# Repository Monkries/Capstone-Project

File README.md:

# Capstone-Project
The lathe is arguably the most important machine tool in engineering history, and one of its defining features is the ability to cut threads. For hundreds of years, this has been accomplished by using gears to link the movement of the cutting tool to the movement of the spinning workpiece. To cut finer or coarser threads, the machinist must vary this gear ratio.This system works, but it has limitations. It is poorly suited for small benchtop machines, because the gearbox parts end up extremely small and expensive to manufacture. It is also inconvenient to adjust; the machinist must read a chart and physically add and remove gears from the geartrain. On larger lathes, this inconvenience is reduced using a simple transmission, allowing the machinist to shift several levers according to a chart, but this is more expensive, and more difficult to scale down to smaller machines.This project aims to replace this gearbox with electronics. This will eliminate the need to physically move gears around to adjust the system; instead, machinists will simply type in the desiredthread pitch into the control panel. Additionally, this system will be much more cost-effective and accessible on small benchtop lathes, where the traditional gearbox approach is impractical.

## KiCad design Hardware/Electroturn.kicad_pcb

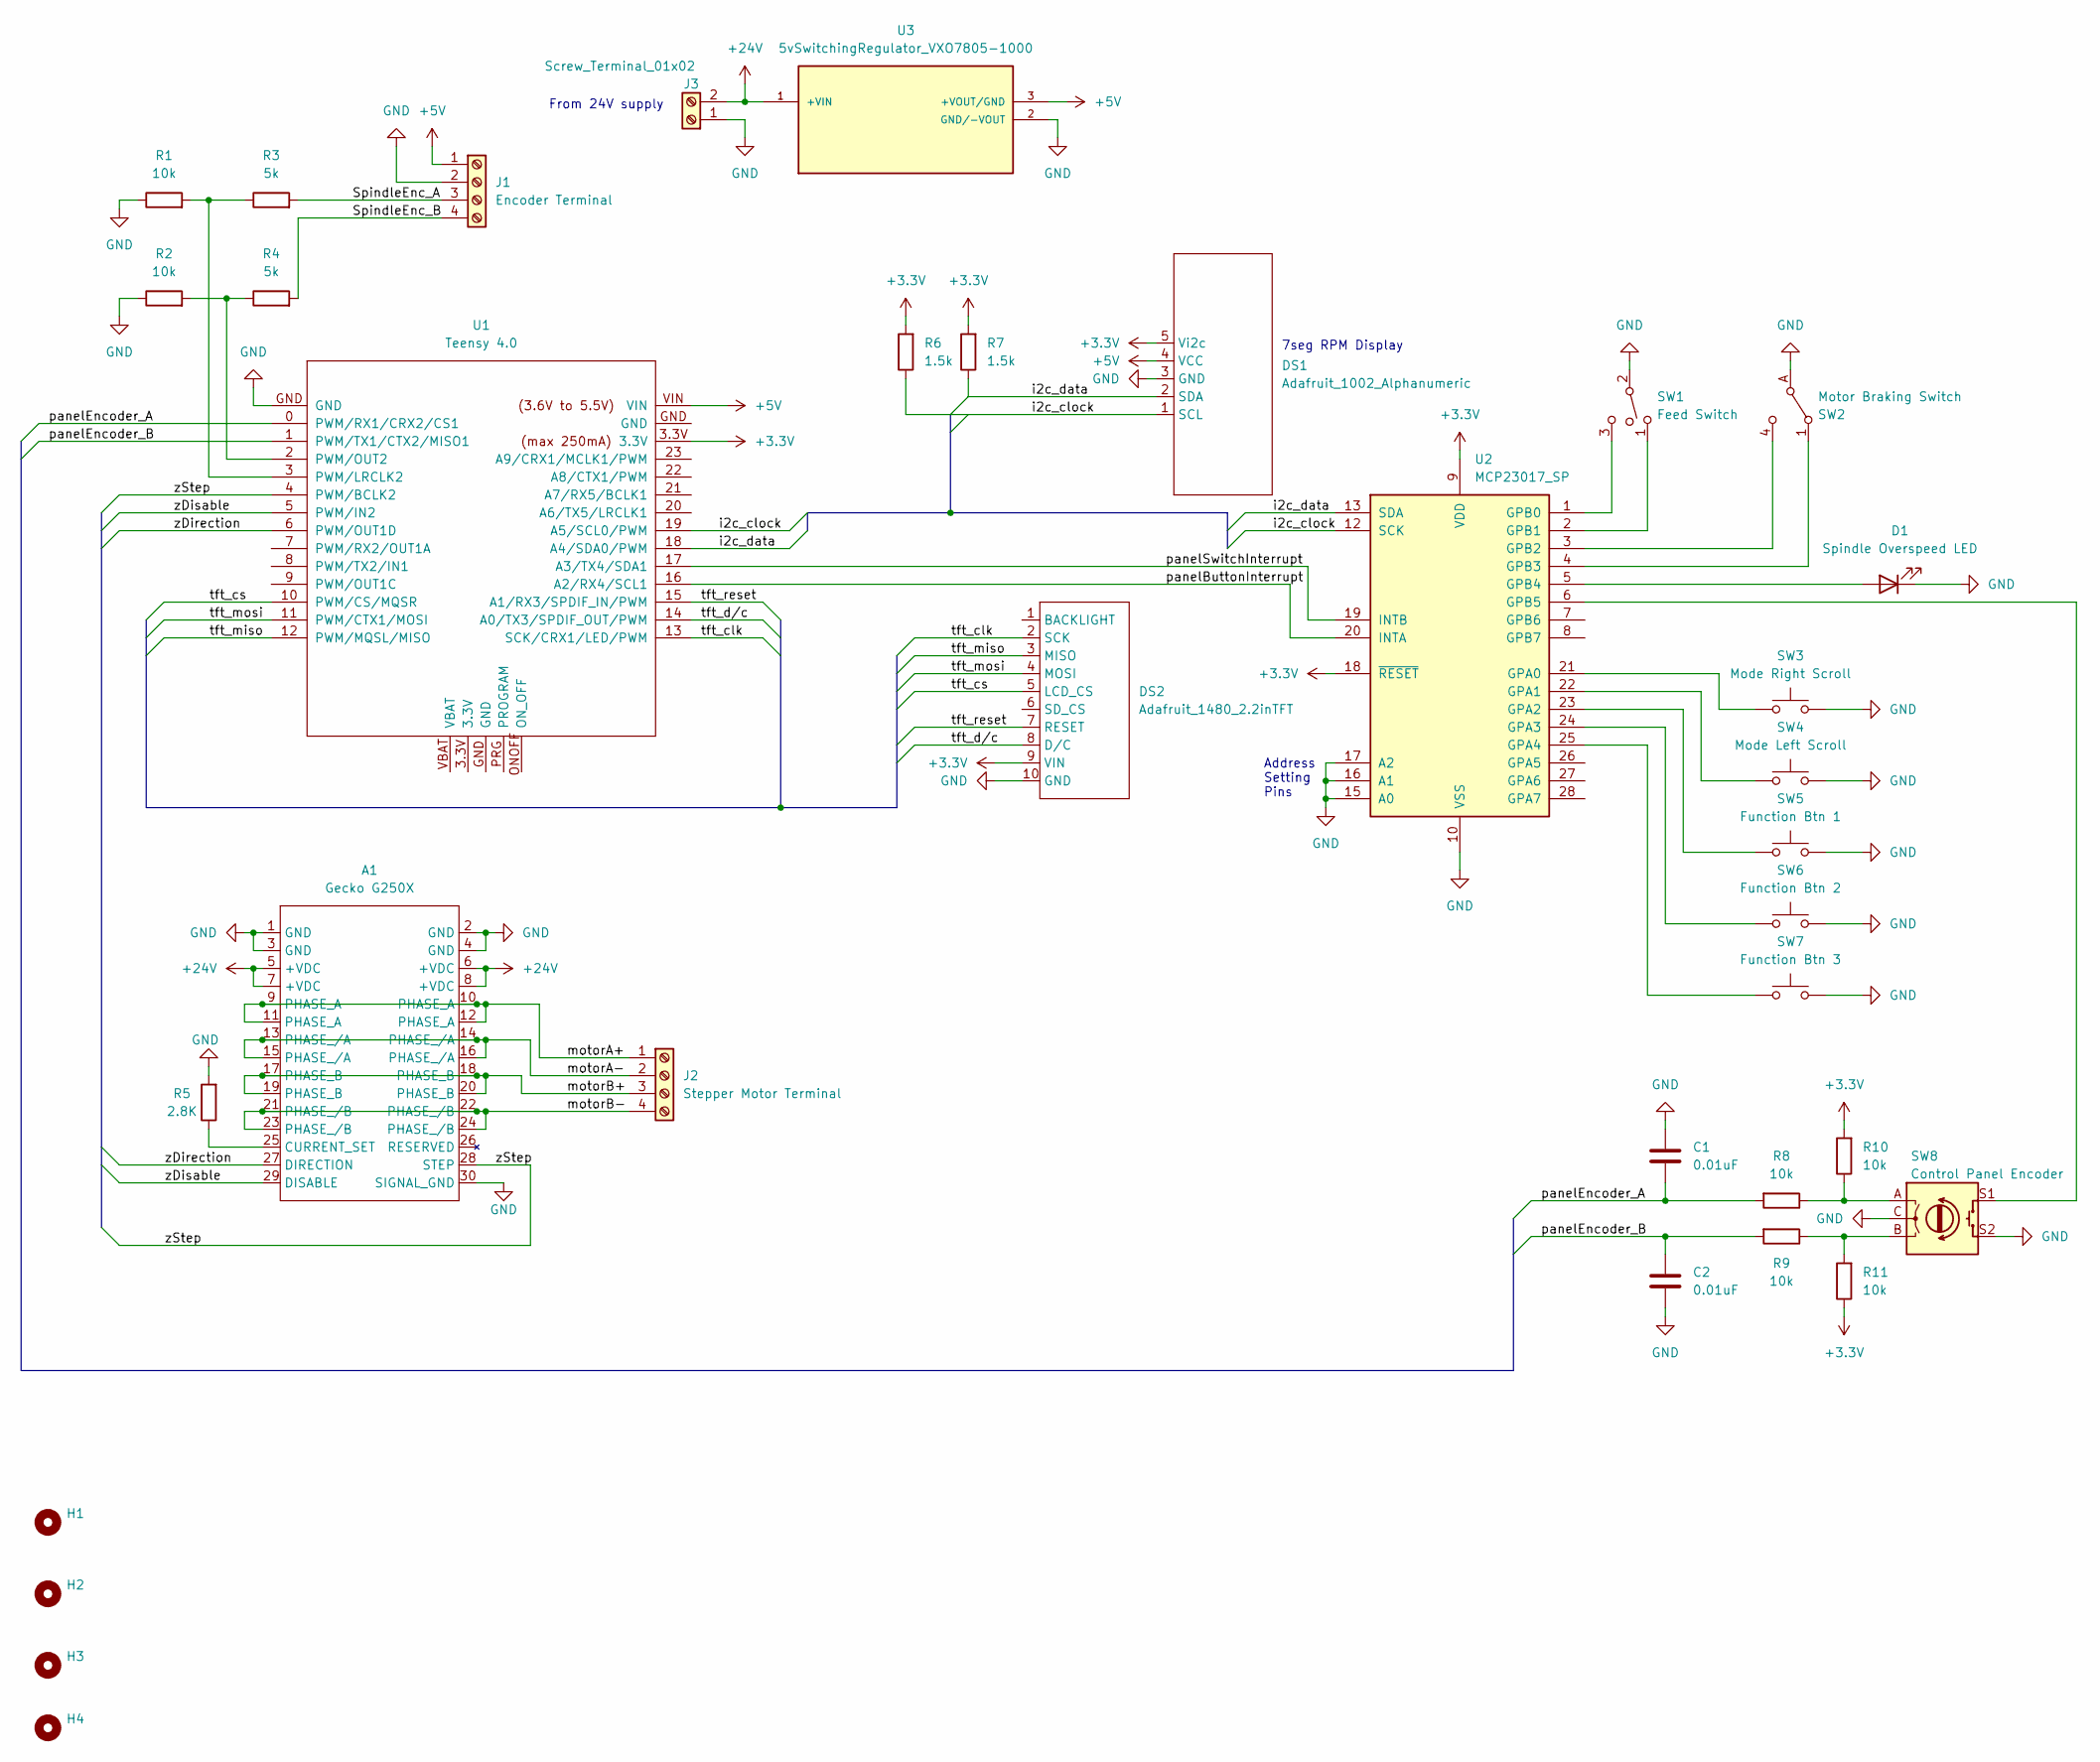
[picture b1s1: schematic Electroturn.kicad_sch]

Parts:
A1: Gecko G250X; GeckoG250XR2_WithHeatsink
C1, C2: 0.01uF; C_Disc_D6.0mm_W2.5mm_P5.00mm
D1: Spindle Overspeed LED; LED_D5.0mm
DS1: Adafruit_1002_Alphanumeric; Adafruit1002_0.54inAlphanumericBackpack
DS2: Adafruit_1480_2.2inTFT; Adafruit1480_TFTwithHeaders
H1, H2, H3, H4: (no value)
J1: Encoder Terminal; ScrewTerminal4_OSTVN04A150
J2: Stepper Motor Terminal; ScrewTerminal4_OSTVN04A150
J3: Screw_Terminal_01x02; 01x02ScrewTerm_OSTVN02A150
R1, R2, R8, R9, R10, R11: 10k; R_Axial_DIN0411_L9.9mm_D3.6mm_P12.70mm_Horizontal
R3, R4: 5k; R_Axial_DIN0411_L9.9mm_D3.6mm_P12.70mm_Horizontal
R5: 2.8K; R_Axial_DIN0411_L9.9mm_D3.6mm_P12.70mm_Horizontal
R6, R7: 1.5k; R_Axial_DIN0411_L9.9mm_D3.6mm_P12.70mm_Horizontal
SW1: Feed Switch; SPDT_OnOffOn_ToggleSwitch_fromECEdepartment_CircularPads
SW2: Motor Braking Switch; SW_SPDT_CK_ A11405RNZQ
SW3: Mode Right Scroll; SW_PUSH_6mm_H9.5mm
SW4: Mode Left Scroll; SW_PUSH_6mm_H9.5mm
SW5: Function Btn 1; SW_PUSH_6mm_H9.5mm
SW6: Function Btn 2; SW_PUSH_6mm_H9.5mm
SW7: Function Btn 3; SW_PUSH_6mm_H9.5mm
SW8: Control Panel Encoder; CUIDevices_ACZ11BR1E20FD112C
U1: Teensy 4.0; Teensy40_OnFemaleHeaders
U2: MCP23017_SP; DIP-28_W7.62mm
U3: 5vSwitchingRegulator_VXO7805-1000; 5vSwitchingRegulator_CONV_VXO7805-1000; PARTREV 1.0

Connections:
+3V3: DS1.5 (Vi2c), DS2.9 (VIN), R6.2, R7.2, R10.2, R11.1, U1.3.3V, U2.9 (VDD), U2.18 (~RESET)
+5V: DS1.4 (VCC), J1.1, U1.VIN, U3.3 (+VOUT/GND)
+24V: A1.5 (+VDC), A1.6 (+VDC), A1.7 (+VDC), A1.8 (+VDC), J3.2, U3.1 (+VIN)
/SpindleEnc_A: J1.3, R3.2
/SpindleEnc_B: J1.4, R4.2
/i2c_clock: DS1.1 (SCL), R6.1, U1.19 (A5/SCL0/PWM), U2.12 (SCK)
/i2c_data: DS1.2 (SDA), R7.1, U1.18 (A4/SDA0/PWM), U2.13 (SDA)
/motorA+: A1.9 (PHASE_A), A1.10 (PHASE_A), A1.11 (PHASE_A), A1.12 (PHASE_A), J2.1
/motorA-: A1.13 (PHASE_/A), A1.14 (PHASE_/A), A1.15 (PHASE_/A), A1.16 (PHASE_/A), J2.2
/motorB+: A1.17 (PHASE_B), A1.18 (PHASE_B), A1.19 (PHASE_B), A1.20 (PHASE_B), J2.3
/motorB-: A1.21 (PHASE_/B), A1.22 (PHASE_/B), A1.23 (PHASE_/B), A1.24 (PHASE_/B), J2.4
/panelButtonInterrupt: U1.16 (A2/RX4/SCL1), U2.20 (INTA)
/panelEncoder_A: C1.2, R8.2, U1.0 (PWM/RX1/CRX2/CS1)
/panelEncoder_B: C2.1, R9.2, U1.1 (PWM/TX1/CTX2/MISO1)
/panelSwitchInterrupt: U1.17 (A3/TX4/SDA1), U2.19 (INTB)
/tft_clk: DS2.2 (SCK), U1.13 (SCK/CRX1/LED/PWM)
/tft_cs: DS2.5 (LCD_CS), U1.10 (PWM/CS/MQSR)
/tft_d/c: DS2.8 (D/C), U1.14 (A0/TX3/SPDIF_OUT/PWM)
/tft_miso: DS2.3 (MISO), U1.12 (PWM/MQSL/MISO)
/tft_mosi: DS2.4 (MOSI), U1.11 (PWM/CTX1/MOSI)
/tft_reset: DS2.7 (RESET), U1.15 (A1/RX3/SPDIF_IN/PWM)
/zDirection: A1.27 (DIRECTION), U1.6 (PWM/OUT1D)
/zDisable: A1.29 (DISABLE), U1.5 (PWM/IN2)
/zStep: A1.28 (STEP), U1.4 (PWM/BCLK2)
GND: A1.1 (GND), A1.2 (GND), A1.3 (GND), A1.4 (GND), A1.30 (SIGNAL_GND), C1.1, C2.2, D1.1 (K), DS1.3 (GND), DS2.10 (GND), J1.2, J3.1, R1.1, R2.1, R5.2, SW1.2, SW2.A, SW3.2, SW4.2, SW5.2, SW6.2, SW7.2, SW8.C, SW8.S2, U1.GND, U2.10 (VSS), U2.15 (A0), U2.16 (A1), U2.17 (A2), U3.2 (GND/-VOUT)
unnamed: A1.25 (CURRENT_SET), R5.1
unnamed: D1.2 (A), U2.5 (GPB4)
unnamed: R1.2, R3.1, U1.3 (PWM/LRCLK2)
unnamed: R2.2, R4.1, U1.2 (PWM/OUT2)
unnamed: R8.1, R10.1, SW8.A
unnamed: R9.1, R11.2, SW8.B
unnamed: SW1.1, U2.2 (GPB1)
unnamed: SW1.3, U2.1 (GPB0)
unnamed: SW2.1, U2.4 (GPB3)
unnamed: SW2.4, U2.3 (GPB2)
unnamed: SW3.1, U2.21 (GPA0)
unnamed: SW4.1, U2.22 (GPA1)
unnamed: SW5.1, U2.23 (GPA2)
unnamed: SW6.1, U2.24 (GPA3)
unnamed: SW7.1, U2.25 (GPA4)
unnamed: SW8.S1, U2.6 (GPB5)

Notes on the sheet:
7seg RPM Display
From 24V supply
Address Setting Pins

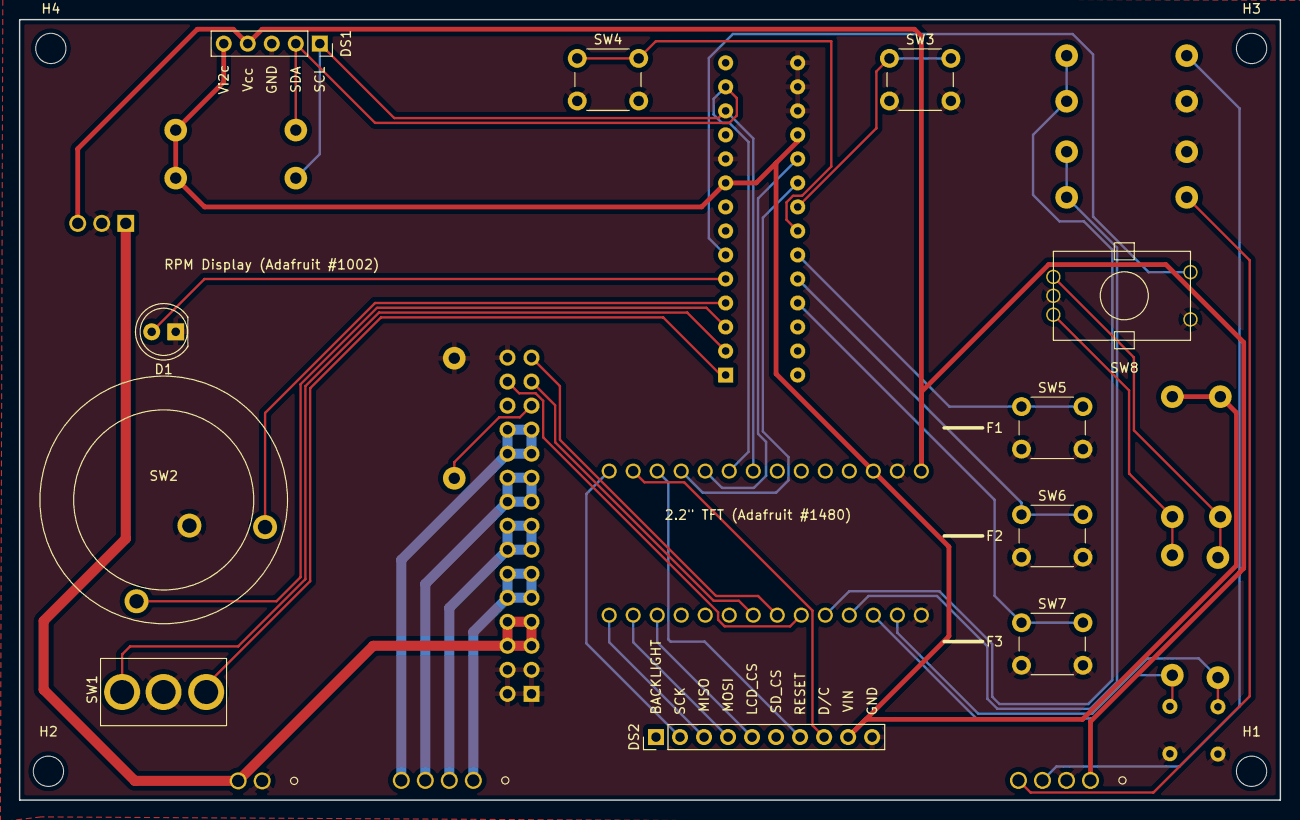
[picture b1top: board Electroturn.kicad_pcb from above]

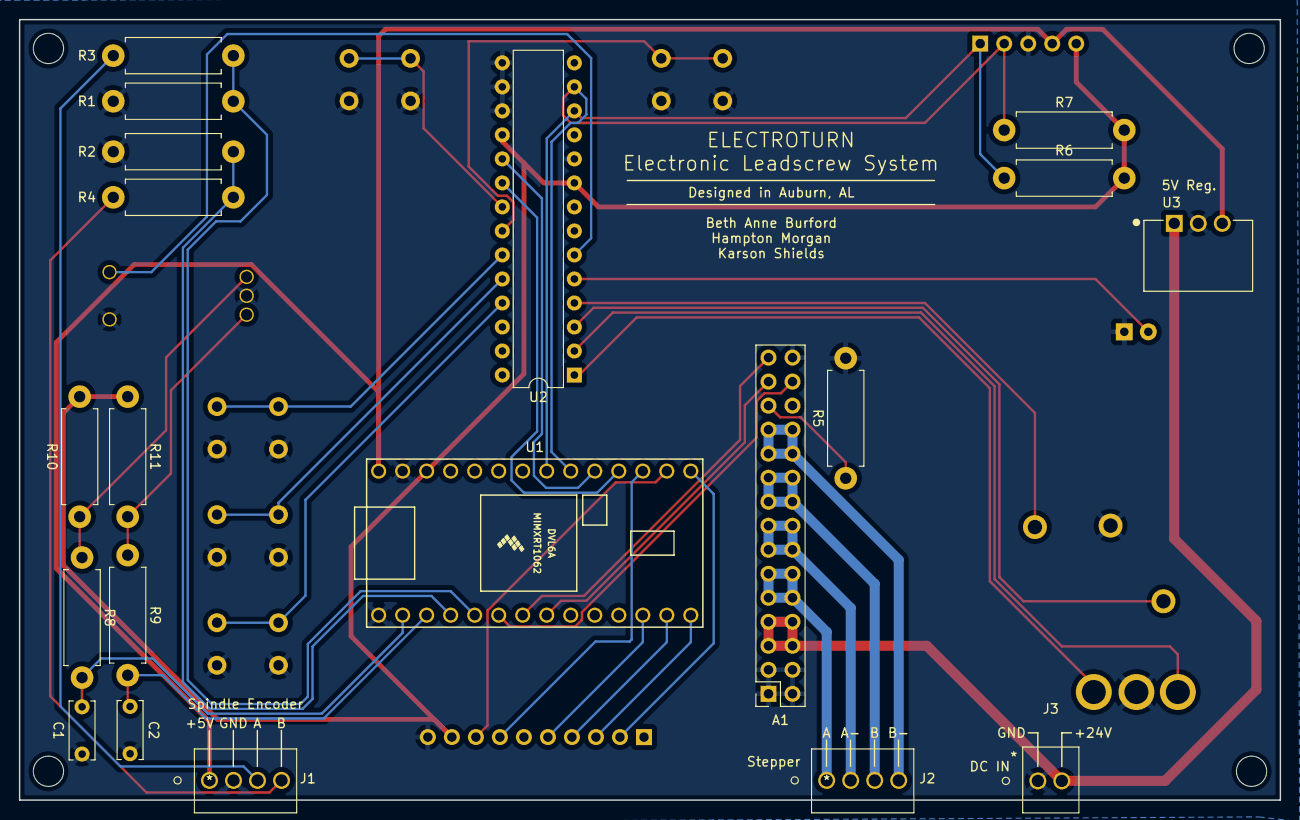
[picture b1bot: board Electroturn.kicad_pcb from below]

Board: 2 copper layers, 133.4 x 82.5 mm, 35 parts (20 on the bottom side), 41 nets.

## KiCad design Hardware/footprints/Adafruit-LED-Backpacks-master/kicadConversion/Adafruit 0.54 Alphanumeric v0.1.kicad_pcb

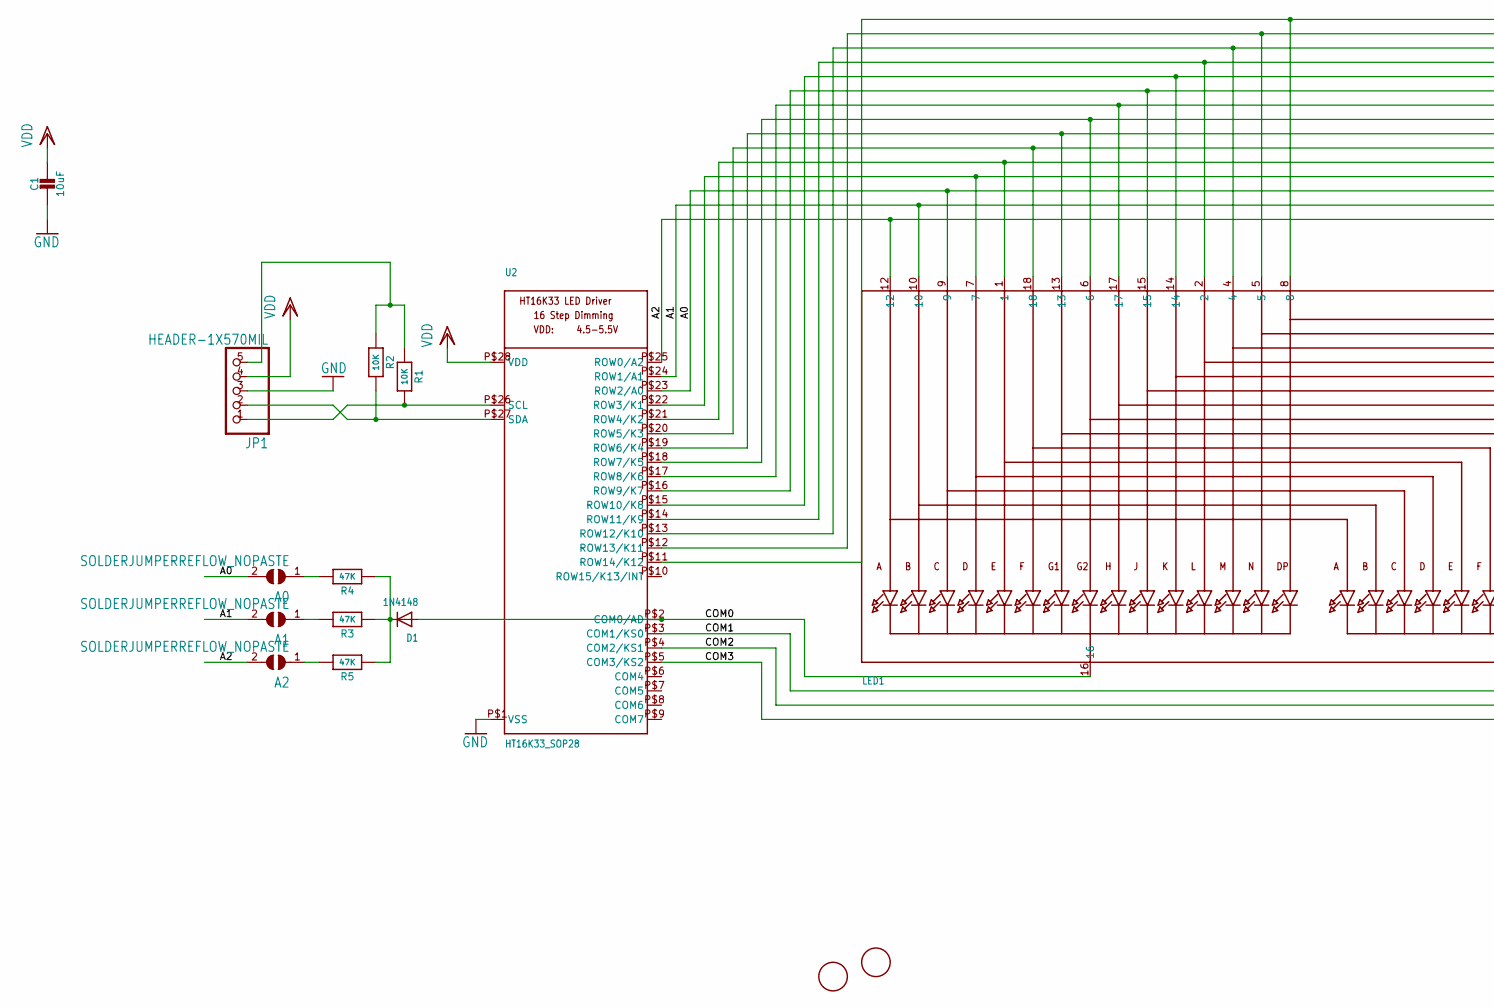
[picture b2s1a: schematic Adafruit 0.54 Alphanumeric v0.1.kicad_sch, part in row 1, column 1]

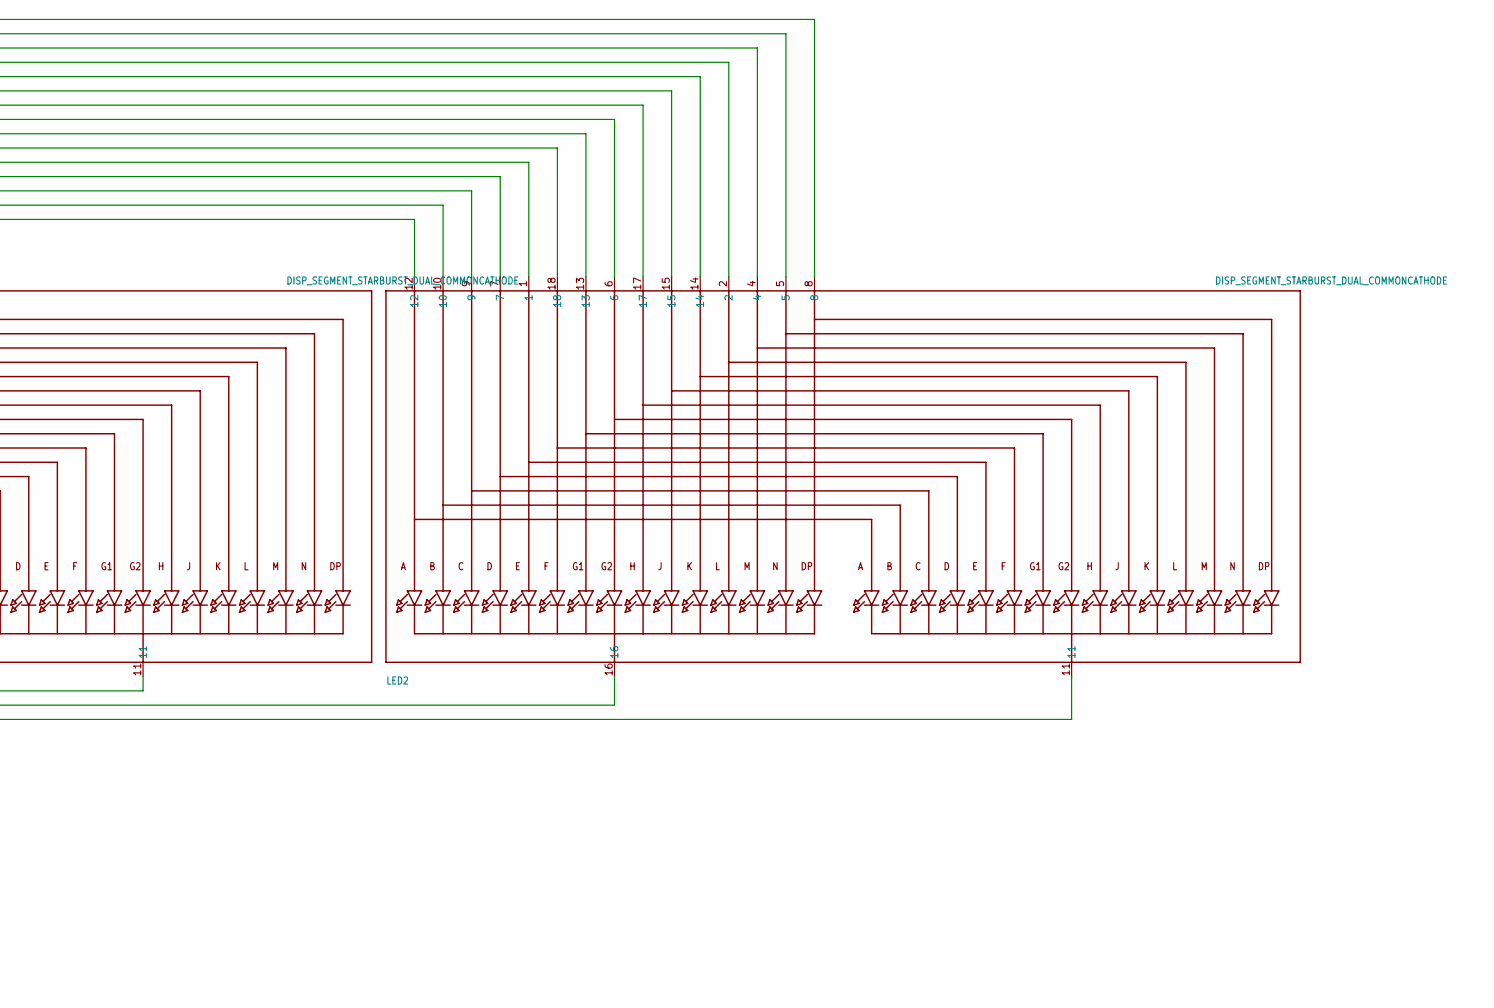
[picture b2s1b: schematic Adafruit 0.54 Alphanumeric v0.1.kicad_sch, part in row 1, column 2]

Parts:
A0, A1, A2: SOLDERJUMPERREFLOW_NOPASTE; SOLDERJUMPER_REFLOW_NOPASTE
C1: 10uF; 0805-NO
D1: 1N4148; SOD-323F
JP1: HEADER-1X570MIL; 1X05_ROUND_70
LED1, LED2: DISP_SEGMENT_STARBURST_DUAL_COMMONCATHODE; SEGMENT_STARTBUST_DUAL_KWA-541CBB
R1, R2: 10K; 0805-NO
R3, R4, R5: 47K; 0805-NO
U2: HT16K33_SOP28; SOP28_300MIL
U$1, U$2: FIDUCIAL; FIDUCIAL_1MM

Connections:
A0: A0.2, LED1.9, LED2.9, U2.P$23 (ROW2/A0)
A1: A1.2, LED1.10, LED2.10, U2.P$24 (ROW1/A1)
A2: A2.2, LED1.12, LED2.12, U2.P$25 (ROW0/A2)
COM0: D1.A, LED1.16, U2.P$2 (COM0/AD)
COM1: LED1.11, U2.P$3 (COM1/KS0)
COM2: LED2.16, U2.P$4 (COM2/KS1)
COM3: LED2.11, U2.P$5 (COM3/KS2)
GND: C1.2, JP1.3, U2.P$1 (VSS)
unnamed: D1.C, R3.1, R4.1, R5.1
unnamed: JP1.5, R1.1, R2.1
unnamed: LED1.17, LED2.17, U2.P$17 (ROW8/K6)
unnamed: LED1.15, LED2.15, U2.P$16 (ROW9/K7)
unnamed: LED1.14, LED2.14, U2.P$15 (ROW10/K8)
unnamed: A2.1, R5.2
unnamed: LED1.2, LED2.2, U2.P$14 (ROW11/K9)
unnamed: LED1.4, LED2.4, U2.P$13 (ROW12/K10)
unnamed: LED1.7, LED2.7, U2.P$22 (ROW3/K1)
unnamed: LED1.1, LED2.1, U2.P$21 (ROW4/K2)
unnamed: LED1.18, LED2.18, U2.P$20 (ROW5/K3)
unnamed: LED1.13, LED2.13, U2.P$19 (ROW6/K4)
unnamed: LED1.5, LED2.5, U2.P$12 (ROW13/K11)
unnamed: LED1.8, LED2.8, U2.P$11 (ROW14/K12)
unnamed: LED1.6, LED2.6, U2.P$18 (ROW7/K5)
unnamed: A1.1, R3.2
unnamed: A0.1, R4.2
SCL: JP1.1, R1.2, U2.P$26 (SCL)
SDA: JP1.2, R2.2, U2.P$27 (SDA)
VDD: C1.1, JP1.4, U2.P$28 (VDD)

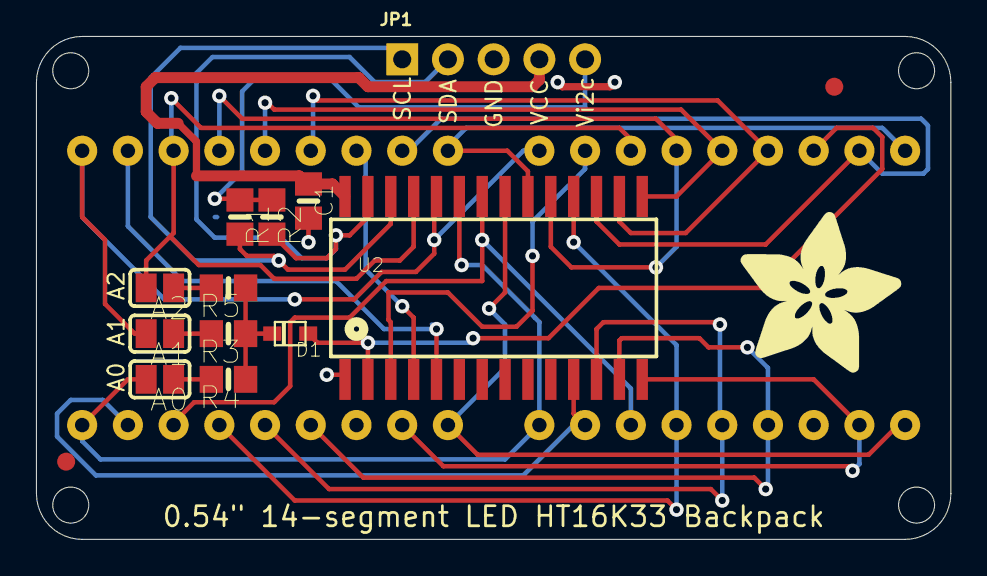
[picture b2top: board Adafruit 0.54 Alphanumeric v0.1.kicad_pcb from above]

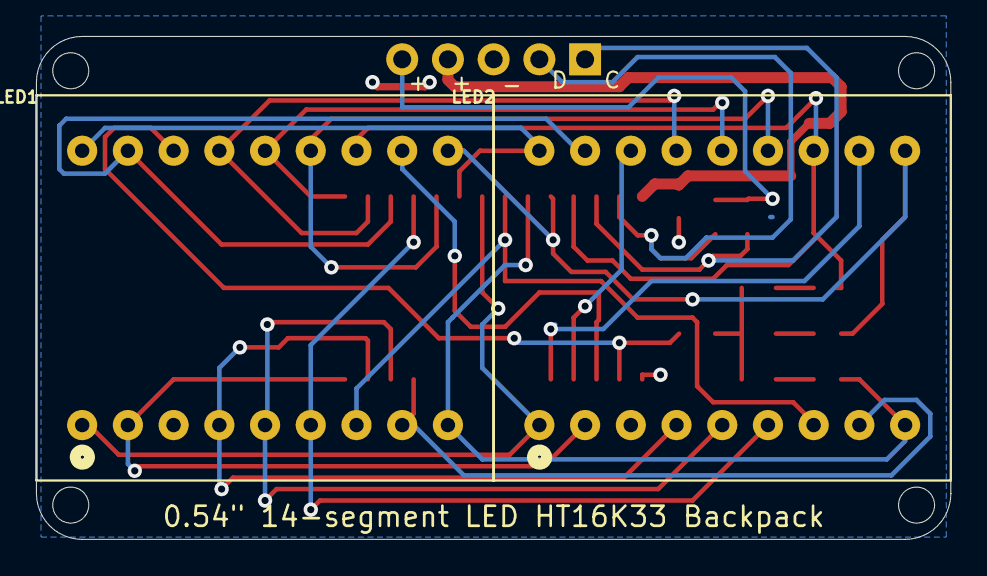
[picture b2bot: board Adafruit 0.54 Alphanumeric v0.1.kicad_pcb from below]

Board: 16 copper layers, 50.8 x 27.9 mm, 21 parts (2 on the bottom side), 28 nets.

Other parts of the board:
@HOLE0, @HOLE1, @HOLE2, @HOLE3: (no value)
U$3: ADAFRUIT_9MM

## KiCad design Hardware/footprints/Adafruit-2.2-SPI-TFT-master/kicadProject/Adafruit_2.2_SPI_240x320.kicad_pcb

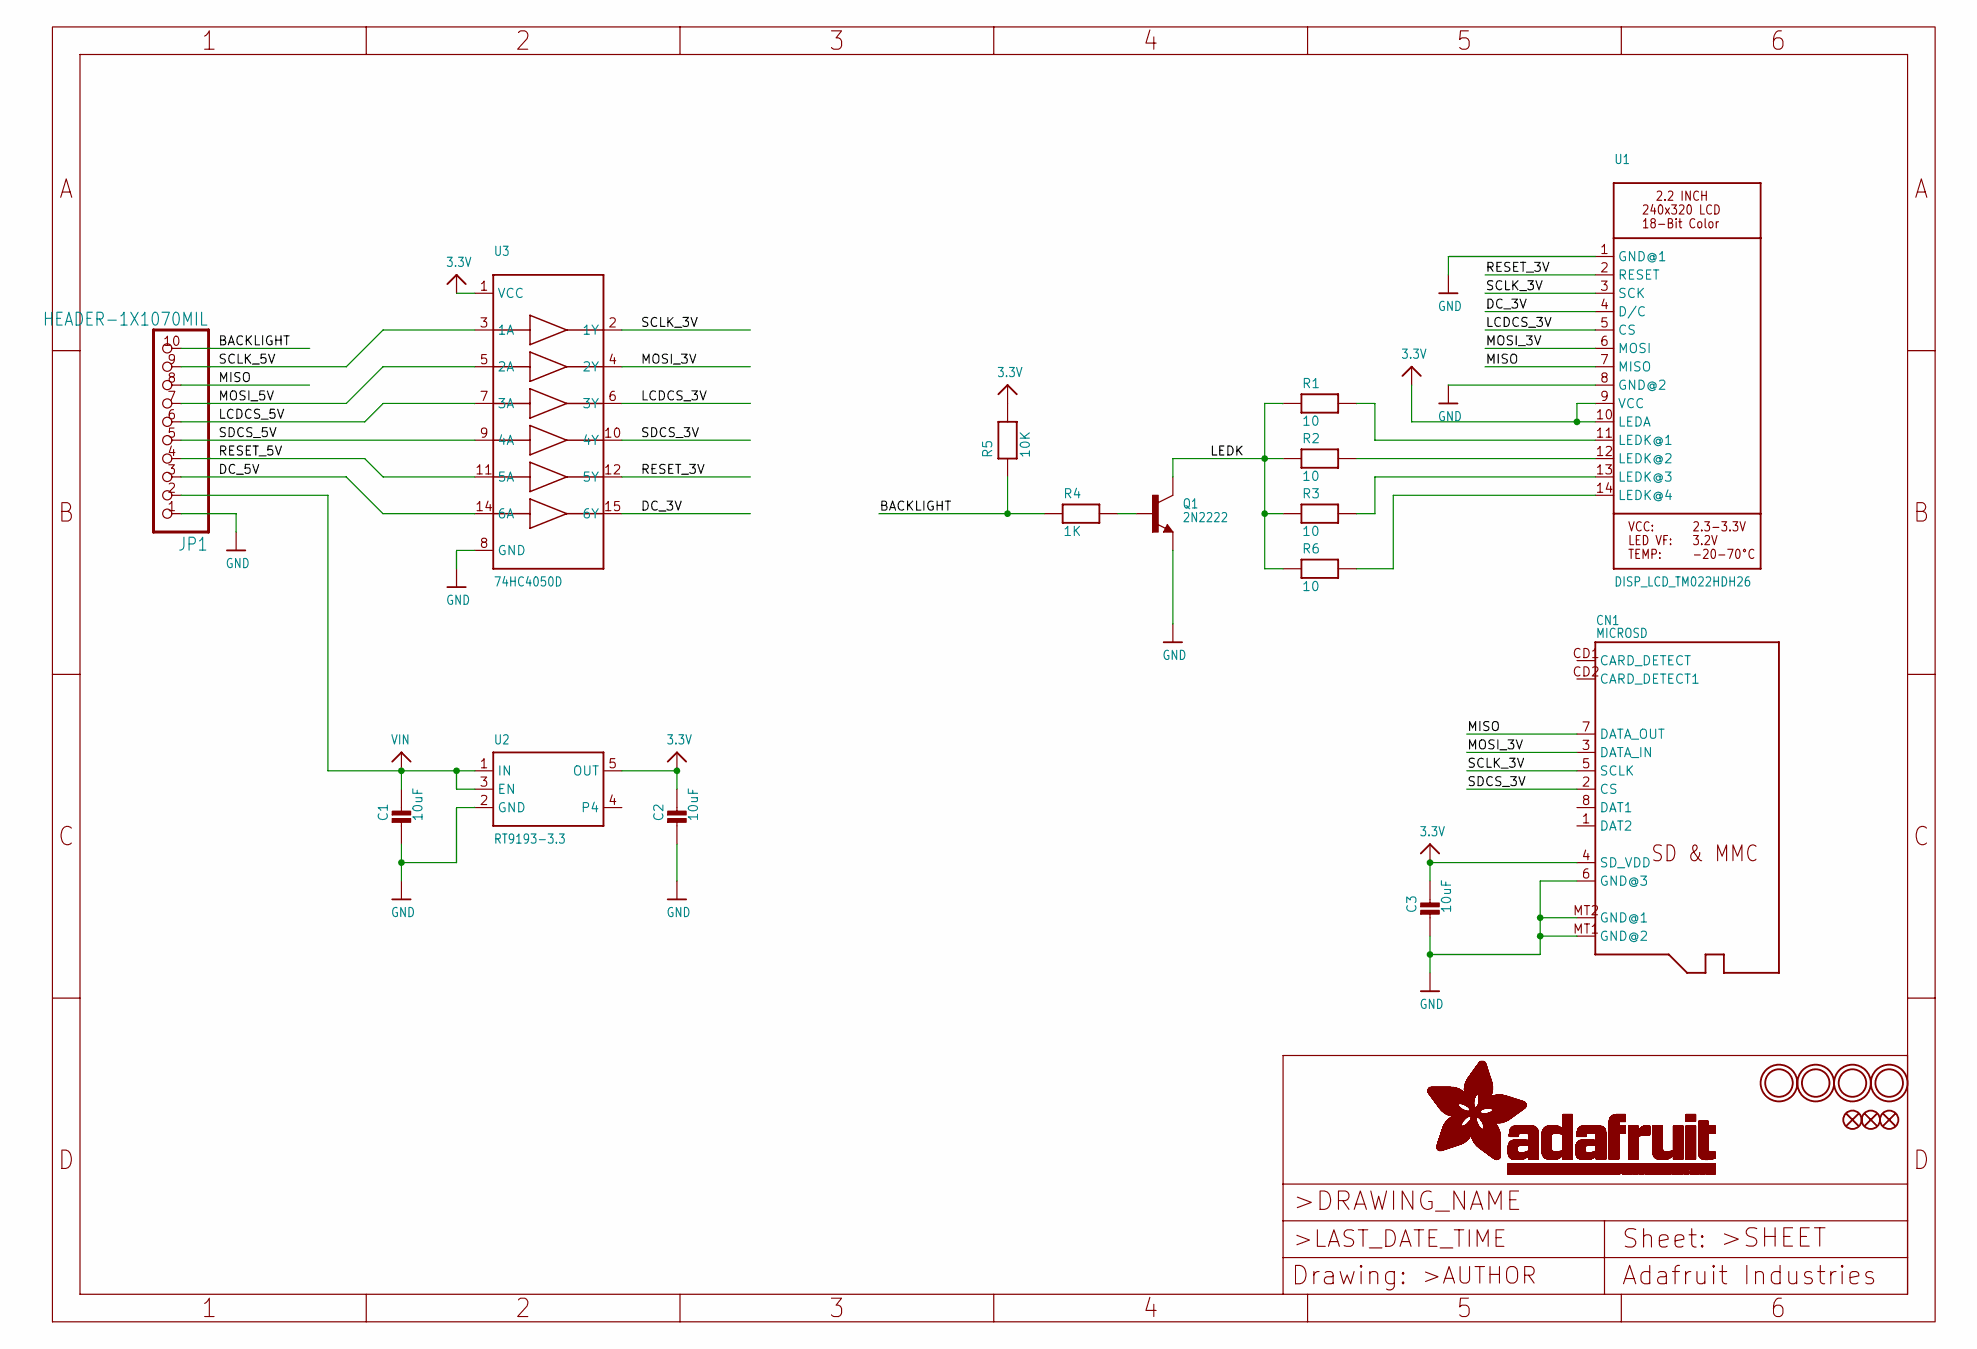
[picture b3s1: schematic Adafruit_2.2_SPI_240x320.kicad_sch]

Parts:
C1, C2, C3: 10uF; _0805MP
CN1: MICROSD
FID1, FID2: FIDUCIAL""; FIDUCIAL_1MM
FID3: EXCLUDE; FIDUCIAL_1MM
JP1: HEADER-1X1070MIL; 1X10_ROUND70
Q1: 2N2222; SOT23-WIDE
R1, R2, R3, R6: 10; _0805MP
R4: 1K; _0805MP
R5: 10K; _0805MP
U1: DISP_LCD_TM022HDH26; TM022HDH26_2.2IN_LCD
U2: RT9193-3.3; SOT23-5
U3: 74HC4050D; SOIC16
U$2, U$3, U$4, U$5: MOUNTINGHOLE2.5; MOUNTINGHOLE_2.5_PLATED

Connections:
3.3V: C2.1, C3.1, CN1.4 (SD_VDD), R5.2, U1.9 (VCC), U1.10 (LEDA), U2.5 (OUT), U3.1 (VCC)
BACKLIGHT: JP1.10, R4.1, R5.1
DC_3V: U1.4 (D/C), U3.15 (6Y)
DC_5V: JP1.3, U3.14 (6A)
GND: C1.2, C2.2, C3.2, CN1.6 (GND@3), CN1.MT1 (GND@2), CN1.MT2 (GND@1), JP1.1, Q1.2 (E), U1.1 (GND@1), U1.8 (GND@2), U2.2 (GND), U3.8 (GND)
LCDCS_3V: U1.5 (CS), U3.6 (3Y)
LCDCS_5V: JP1.6, U3.7 (3A)
LEDK: Q1.3 (C), R1.1, R2.1, R3.1, R6.1
MISO: CN1.7 (DATA_OUT), JP1.8, U1.7 (MISO)
MOSI_3V: CN1.3 (DATA_IN), U1.6 (MOSI), U3.4 (2Y)
MOSI_5V: JP1.7, U3.5 (2A)
unnamed: R1.2, U1.11 (LEDK@1)
unnamed: R2.2, U1.12 (LEDK@2)
unnamed: R3.2, U1.13 (LEDK@3)
unnamed: Q1.1 (B), R4.2
unnamed: R6.2, U1.14 (LEDK@4)
RESET_3V: U1.2 (RESET), U3.12 (5Y)
RESET_5V: JP1.4, U3.11 (5A)
SCLK_3V: CN1.5 (SCLK), U1.3 (SCK), U3.2 (1Y)
SCLK_5V: JP1.9, U3.3 (1A)
SDCS_3V: CN1.2 (CS), U3.10 (4Y)
SDCS_5V: JP1.5, U3.9 (4A)
VIN: C1.1, JP1.2, U2.1 (IN), U2.3 (EN)

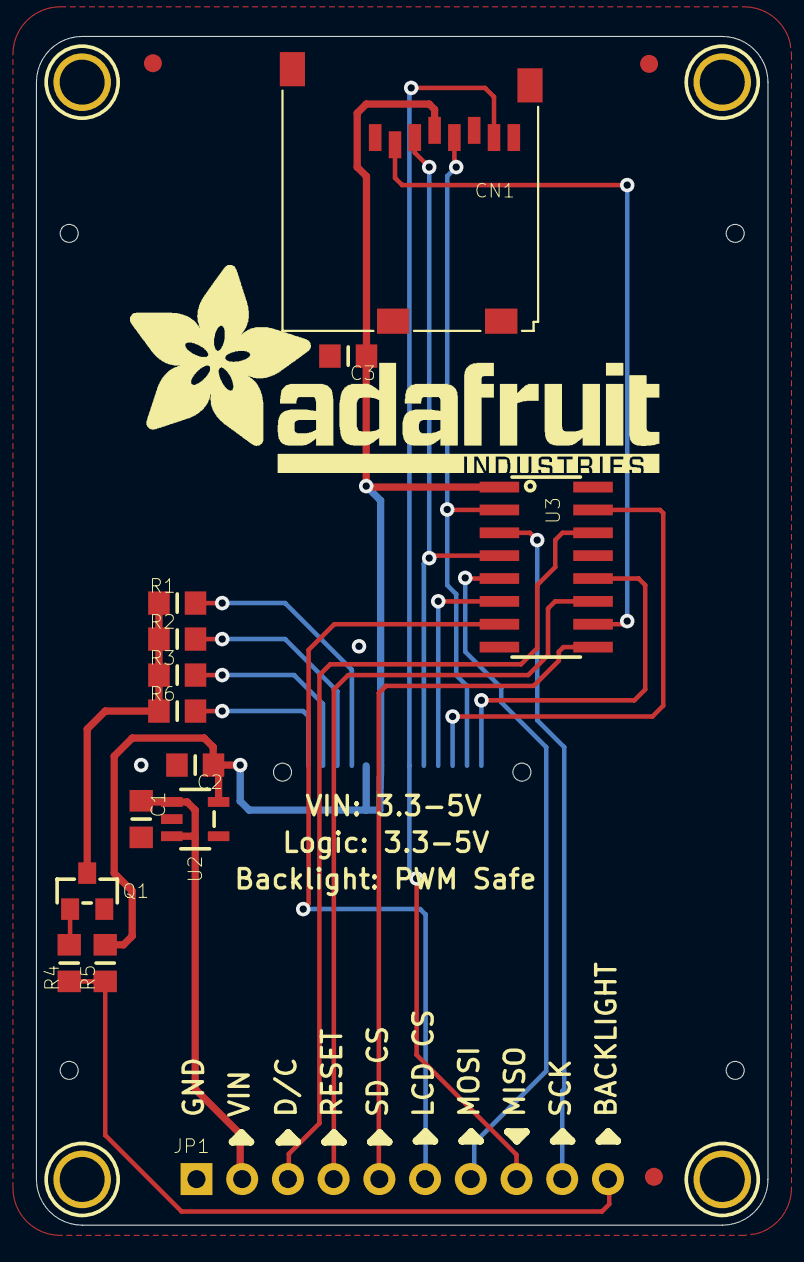
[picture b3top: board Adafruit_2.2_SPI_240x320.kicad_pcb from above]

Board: 2 copper layers, 40.6 x 66.0 mm, 23 parts (1 on the bottom side), 23 nets.

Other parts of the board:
U$20: ADAFRUIT_TEXT_30MM

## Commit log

2021-10-05 Create test
2021-10-11 test run of commiting
2021-10-11 vscode settings
2021-10-11 added a vairable for the return value
2022-01-24 Testing my privileges
2022-01-24 Reorganizing, adding beginning of KiCad work
2022-01-26 Converting Teensy library to newer format
2022-01-26 Improving Teensy 4.0 symbol
2022-01-26 Setting up Arduino project, testing encoder in software
2022-02-06 Initial encoder and stepper test code
2022-02-07 Initial layout ideas, spindle speed computation
2022-02-13 Adding 8 pin aviation connector to KiCad schematic
2022-02-17 Framework of code for inital development
2022-02-19 Migrating to PlatformIO, reorganizing
2022-02-21 Roughing out modes, power feed code
2022-02-22 Removing local IDE config files from Git tracking
2022-02-27 Starting to build out backend leadscrew library
2022-02-27 2-27 Meeting: Roughing out backend lib
2022-02-27 Docs changes from 2-27 meeting
2022-02-28 Simple example commit for Beth Anne
2022-02-28 Undoing changes from previous example commit
2022-02-28 We are having a hard time
2022-02-28 Deleted
2022-03-02 Adding user interface states documentation
2022-03-04 Gear ratio computation, changed function types
2022-03-15 Renaming cfg_ constants to sys_
2022-03-16 Data type refactoring (!usable code right now)
2022-03-16 Got referencing issues fixed, backend has access to hardware now!
2022-03-17 Beth Annes kicad work part 1
2022-03-17 Beth Annes work deleting unnecessary folder
2022-03-17 Adding Adafruit TFT library and dependencies
2022-03-17 Adjusting control panel display schematic
2022-03-17 Formatting of displays v1
2022-03-18 Reorganize
2022-03-18 Dealing with "remainder" steps
2022-03-21 Added LED backpack library and removed separate 7seg display libraries
2022-03-21 Adding missing RST pin for TFT display in KiCad schematic
2022-03-21 Renaming/restructuring control panel lib
    This is a skeleton of the control panel lib, and I think the display objects (for the TFT and the alphanum) are both created correctly now. Haven't tested on actual hardware yet.
2022-03-21 Adding a few more comments
2022-03-22 Formatted code into new skeleton
2022-03-22 Test code
2022-03-22 Testing shenanigans
2022-03-23 Adding pulley multiplier to leadscrew backend
2022-03-23 Finishing calculateMotorSteps
2022-03-24 Text Display fucntional, added I2C lib but still wip for alphanueric
2022-03-24 Got rid of code trying to do the alphanum display. Waiting for more help from adafruit now
2022-03-24 Work on virtual clutch (semi successful) This works, with some error, but the error seems to be speed dependent. Not sure if this is programming error (more "lost" data with higher speeds) or error i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
2022-03-25 Added splashscreen, fixed format of display
2022-03-26 Removing unnecessary i2c lib
2022-03-26 Fleshing out elsControlPanel.alphanum_writeRPM()
2022-03-27 New branch for pcb work
2022-03-27 Something like a pcb?
2022-03-28 Adding 3D models, improving footprints for Teensy and Gecko, adding screw terminals to schematic
2022-03-28 partial enum work
2022-03-28 Enums setup
2022-03-29 Tidying Karson's enum work
2022-03-29 Adding MCP23017 (i2c IO chip) to schematic, other housekeeping
2022-03-29 Consolidating most things into buses on schematic
2022-03-29 Fixed formating issues for TFT and changed TFT test code
2022-03-29 Edited comments, changed argumens of LED function
2022-03-29 Adding whole .vscode dir to gitignore
2022-03-29 Adding IntegerStepHelper library
2022-03-30 Temporarily reversing system for sync test
2022-03-30 Working test code using absolute coordinates, not sure why relative motion doesn't work right
2022-03-30 Preliminary working clutch code (unidirectional)
2022-03-30 Fixing mislabeled interrupt pins
2022-03-30 Fixing R values in panel encoder voltage divider
2022-03-30 Adding proper GitIgnore for KiCAD
2022-03-30 Removing newly ignored KiCAD cache files
2022-03-30 Adding gitignore for KiCAD
2022-03-30 Removing newly ignored KiCAD files
2022-03-30 Reorganizing KiCAD repo, fixing path issues
    I tidied up the folder structure, and also went in and relinked all the footprints/symbols using the correct new paths. Should work across any system now. Also linked the appropriate 3D models for th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
    I updated the PCB to include all these new changes from the footprints/schematic, and in doing so it pretty much destroyed what Karson had...sorry Karson
2022-03-31 Removing old leftovers from TeensyLeadscrew
2022-03-31 Testing of all displays
2022-03-31 Changed name for buttons
2022-03-31 Adding connection to schematic, test code for buttons
2022-04-02 Removing KiCad edit commit: "Changed name for buttons"
    This reverts commit c135a4e2cf57f768540b1a317894a2067f308fdb.
2022-04-02 Reverting change to KiCad schematic to prevent merge issues
2022-04-02 Moving gearbox info into struct, tidying
2022-04-02 I think clutch is working, no direction awareness
2022-04-02 Removing stray serial.print
2022-04-02 Separating clutch logic: initial working test
2022-04-02 Working both directions, constraining angles right
2022-04-02 Finishing up on Saturday
2022-04-03 Added button functions, changed a few function args
2022-04-03 Buttons done minus units
2022-04-03 Beth Anne's footprint designs
2022-04-03 Housekeeping in the clutch class
2022-04-03 Adding tolerance math to clutch locking
2022-04-03 Removing tolerance math (unforeseen issues need lots of careful testing)
2022-04-04 Adding encoder filter circuit, assuming 5V operation (subject to change)
2022-04-04 Fixing Rotarty Switch Footprint
2022-04-04 Adding pin numbers to adafruit TFT symbol
2022-04-04 Adding 3D model and footprint for TFT
2022-04-04 Adding alphanumeric display footprint
2022-04-04 More footprint work
2022-04-04 Debouncing stuff?, fixed display
2022-04-05 Adding footprint for SPDT feed switch from ECE dept
2022-04-05 Quick Fix: swapping panel encoder to 3.3V
2022-04-05 Fixing broken symbol links from merge
2022-04-05 Quick fixes: schematic housekeeping
2022-04-05 Initial PCB work
2022-04-05 Adding symbol and footprint for 5V regulator
2022-04-05 Adding 5V regulator to schematic
2022-04-05 Adding 1x2 screw terminal footprint, assigning 3D models
2022-04-05 Footprint housekeeping, updating PCB components
2022-04-05 Adding design rules for PCB milling
    Adding design rules based on Bantam's Othermill (the Haas is probably way more accurate than that, but I'm taking this conservatively)
2022-04-05 Locking major control panel UI components
2022-04-05 Revert "Initial PCB work" to prevent KiCad merge hell
    This reverts commit 830c4b3218d3f5d7a4b251521e18afe8c7a9bcf8.
2022-04-05 Importing corrected footprint for rotary switch
2022-04-05 Adding 3D model for rotary switch
2022-04-05 Updating rotary switch footprint on PCB
2022-04-05 Some placement work
2022-04-05 correcting mislabeled function button
2022-04-05 Initial placements
2022-04-05 Adding net classes for PCB traces
2022-04-05 Fixing schematic parity issues with PCB footprints
2022-04-05 PCB is routed
2022-04-05 Adding mounting holes, starting to generate gerbers
2022-04-06 Adding mounting holes and re-exporting Gerbers and STEP
2022-04-06 A little sketching in the cpanel class
2022-04-06 Adding MCP23017 button mappings to enum
2022-04-06 More design cleanup in control panel class
2022-04-08 Temporary feed switch code for testing on lathe
2022-04-09 Commenting TeensyLeadscrew and clutch class
2022-04-09 Adding clutch info to README
2022-04-11 Code Reorg stuff
2022-04-11 LED stuff
2022-04-11 Changing variables and such
2022-04-11 Cleaning up unbuildable code in main.cpp
2022-04-11 More cleaning up in main.cpp
2022-04-12 Adding rough outline for main.cpp UI logic
2022-04-12 More outlining work
2022-04-12 Prep work for programming session in elsControlPanel
2022-04-13 Setup basic work flow, changed TFT layout, debounce buttons stuff
2022-04-13 Removes comments and formating
2022-04-13 comments
2022-04-18 Prepping for Karson's switch work
2022-04-18 Switch debounce updating and attaching
2022-04-18 Cleaning up typos, adding test code for UI inputs, all buttons and switches working
2022-04-18 Beginning to add business logic, fixing error in tachometer math
2022-04-19 Working test code for interrupt timer method
2022-04-19 Removing printAllInputs
2022-04-19 My initial UI logic - partly working
2022-04-19 Panel encoder, units, and feed clutch working
2022-04-19 Mostly working, getting ready to remove direction awareness
2022-04-20 Working-ish test code
2022-04-20 Adding overspeed LED code (untested)
2022-04-20 Adding motor braking controls (tested, working)
2022-04-22 Slight display changes
2022-04-22 Housekeeping in main.cpp, deleting TeensyDebug lib
2022-04-23 Adjusting display font size, fixing encoder noise issues
2022-04-23 Removing rapid text from display
2022-04-23 Adding proper overspeed lockout
2022-04-24 Removing non-working attempt at making motor braking smarter
2022-04-24 Initial code for fixing clutch placement in overall system
2022-04-25 Adding examples of how to use backend code
2022-04-29 Changed some comments

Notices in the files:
parts and their libraries:
Copyright 2021 Accelerated Designs. All rights reserved.
